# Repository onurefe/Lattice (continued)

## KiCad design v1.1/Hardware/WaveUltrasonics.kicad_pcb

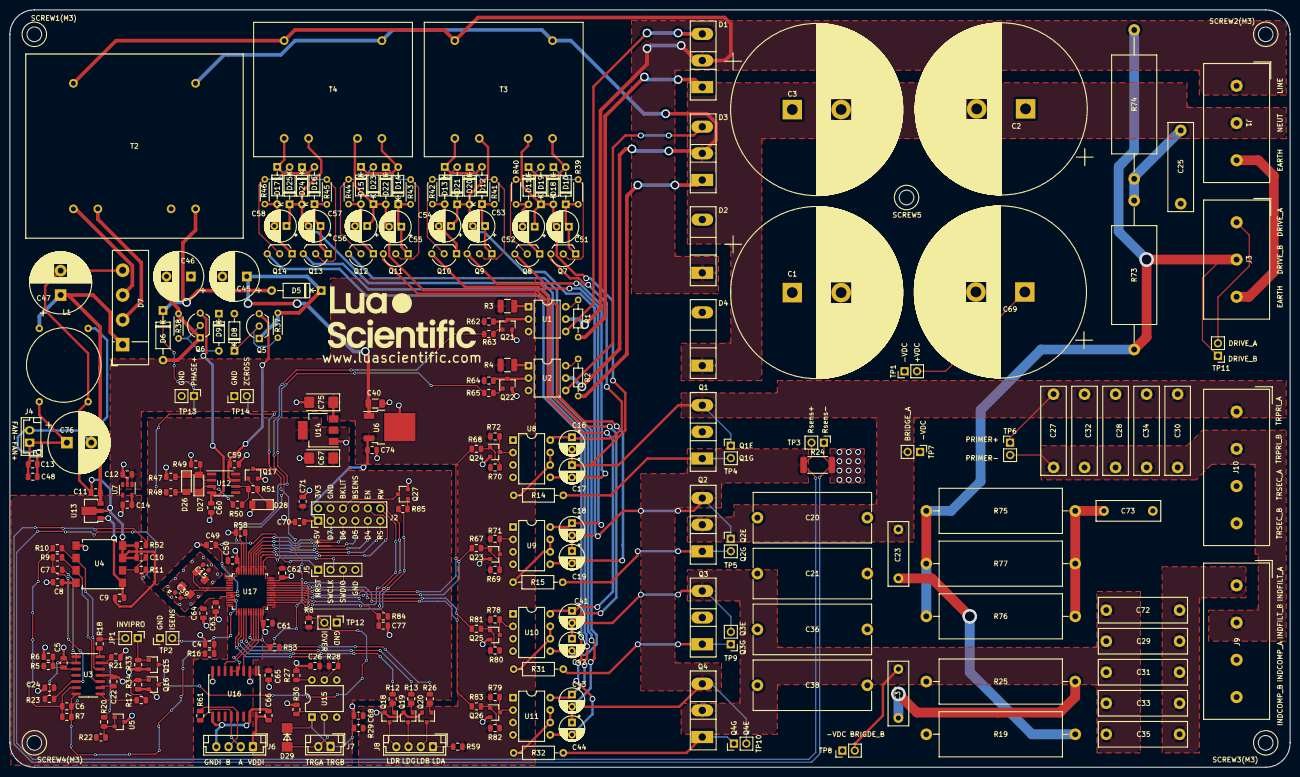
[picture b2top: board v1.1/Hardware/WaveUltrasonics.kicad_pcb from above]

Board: 2 copper layers, 262.0 x 155.0 mm, 257 parts (0 on the bottom side), 155 nets.

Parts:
C1, C2, C3, C69: 470u 400v; CP_Radial_D35.0mm_P10.00mm_SnapIn
C4: 100n; R_0805_2012Metric
C5, C11, C12, C13, C14, C63: 1u; C_0805_2012Metric
C6, C7: 330p; C_0805_2012Metric
C8, C9, C24, C26, C48, C49, C50, C59, C60, C61, C62, C64, C65, C66, C68, C70, C71, C74, C77: 100n; C_0805_2012Metric
C10: 47n; C_0805_2012Metric
C15, C39: 18p; C_0603_1608Metric
C16, C17, C18, C19, C41, C42, C43, C44: 1u 35v; CP_Radial_D5.0mm_P2.50mm
C20, C21, C36, C38: 820n 400VDC; C_Rect_L24.0mm_W10.1mm_P22.50mm_MKT
C22: 2.2u; C_0805_2012Metric
C23, C37, C73: 2.2n 400VAC; C_Rect_L13.0mm_W4.0mm_P10.00mm_FKS3_FKP3_MKS4
C25: 1.5n 400VAC; C_Rect_L18.0mm_W5.0mm_P15.00mm_FKS3_FKP3
C27, C28, C30, C32, C34: 6.8n 400VAC; C_Rect_L18.0mm_W5.0mm_P15.00mm_FKS3_FKP3
C29, C31, C33, C35, C72: 10n; C_Rect_L18.0mm_W5.0mm_P15.00mm_FKS3_FKP3
C40: 1uF 35v; C_1206_3216Metric
C45, C46: 470u 35v; CP_Radial_D10.0mm_P5.00mm
C47, C76: 1000u 35v; CP_Radial_D12.5mm_P5.00mm
C51, C52, C53, C54, C55, C56, C57, C58: 220u; CP_Radial_D6.3mm_P2.50mm
C67, C75: 10uF; CP_EIA-6032-15_Kemet-U
D1, D3: CLA50E1200HB; TO-247-3_Vertical
D2, D4: DSEI60-06A; TO-247-2_Vertical
D5, D6: 1N4007; D_A-405_P10.16mm_Horizontal
D7: D_Bridge_+AA-; Diode_Bridge_Vishay_KBU
D8, D9, D18, D19, D20, D21, D22, D23, D24, D25: 15v; D_DO-35_SOD27_P7.62mm_Horizontal
D10, D11, D12, D13, D14, D15, D16, D17: D; D_DO-35_SOD27_P7.62mm_Horizontal
D26, D27, D28: D; D_MiniMELF
D29: SMAJ6R0CA-HT; DO214AC_SMA
J1: MAINS_IN; DG25C-B-03P-13-00AH
J2: L-KLS1-207-2-12-S; PinHeader_2x06_P2.54mm_Vertical
J3: Screw_Terminal_01x03; DG25C-B-03P-13-00AH
J4, J7: DS1069-02MVW6X; JST_EH_B2B-EH-A_1x02_P2.50mm_Vertical
J5: Conn_01x04; PinHeader_1x04_P2.54mm_Vertical
J6, J8: DS1069-04MVW6X; JST_EH_B4B-EH-A_1x04_P2.50mm_Vertical
J9, J10: DG25C-B-04P-13-00AH
JP1: Jumper_NO_Small; PinHeader_1x02_P2.54mm_Vertical
L1: EMIFilter_LL_2314; EPCOS_B82721A
Q1, Q2, Q3, Q4: IXXH80N65B4H1; TO-247-3_Vertical
Q5, Q7, Q9, Q11, Q13: BC546; TO-92_Inline_Wide
Q6, Q8, Q10, Q12, Q14: BC556; TO-92_Inline_Wide
Q15, Q16, Q17, Q18, Q19, Q20: MMBT3904; SOT-23
Q21, Q22, Q23, Q24, Q25, Q26, Q27: BC817; SOT-23
R1, R2: 1.5k; R_Axial_DIN0204_L3.6mm_D1.6mm_P7.62mm_Horizontal
R3, R4: 51R 1/2Watt; R_1210_3225Metric
R5, R6, R21: 22k %0.1; R_0805_2012Metric
R7, R23: 3.6k %0.1; R_0805_2012Metric
R8, R29, R30, R53, R61, R67, R68, R81, R83, R84: 120R; R_0805_2012Metric
R9, R10: 4.7k %0.1; R_0805_2012Metric
R11: 10R; R_0805_2012Metric
R12, R13, R26, R27, R58: 10k; R_0805_2012Metric
R14, R15, R31, R32: 10R; R_Axial_DIN0207_L6.3mm_D2.5mm_P10.16mm_Horizontal
R16: 33R; R_0805_2012Metric
R17, R18, R22, R28, R63, R65, R85: 2.2k; R_0805_2012Metric
R19, R25: 15R 5W; R_Axial_Power_L25.0mm_W9.0mm_P30.48mm
R20: 20k %0.1; R_0805_2012Metric
R24: 6.8mohm 2W %1; R_2512_6332Metric
R33, R34: 1k; R_0805_2012Metric
R37, R38, R39, R40, R41, R42, R43, R44, R45, R46: 1k; R_Axial_DIN0204_L3.6mm_D1.6mm_P5.08mm_Horizontal
R47, R48, R51, R62, R64: 4.7k; R_0805_2012Metric
R49, R50: 1M; R_0805_2012Metric
R52: 0R; R_0805_2012Metric
R59: 220R; R_0805_2012Metric
R69, R70, R80, R82: 8.2k; R_0805_2012Metric
R71, R72, R78, R79: 82R; R_0805_2012Metric
R73, R74: 22k 7W; R_Axial_DIN0922_L20.0mm_D9.0mm_P30.48mm_Horizontal
R75, R76, R77: 4.7k 5W; R_Axial_Power_L25.0mm_W9.0mm_P30.48mm
T2: Transformer_1P_2S; ASL151212
T3, T4: Transformer_1P_2S; ASL102212
TP1, TP2, TP3, TP4, TP5, TP6, TP7, TP8, TP9, TP10, TP11, TP12, TP13, TP14: TestPoint_2Pole; PinHeader_1x02_P2.54mm_Vertical
U1, U2: 4N39; DIP-6_W7.62mm
U3: MCP6024; SOIC-14_3.9x8.7mm_P1.27mm
U4: ACPL-7900; SSO-8_6.7x9.8mm_P2.54mm_Clearance8mm
U5: TL431LP; SOT-23
U6: L7805; TO-252-2
U7: TLV73333PDBV; SOT-23-5
U8, U9, U10, U11: HCPL-3120; DIP-8_W7.62mm
U12: OPA228; SOIC-8_3.9x4.9mm_P1.27mm
U13: L78L05_SOT89; SOT-89-3
U14: TLV1117-33; SOT-223-3_TabPin2
U15: 4N25; DIP-6_W7.62mm
U16: ADM2483xRW; SOIC-16W_7.5x10.3mm_P1.27mm
U17: STM32F334C8Tx; LQFP-48_7x7mm_P0.5mm
Y1: 8MHz; Crystal_5x3.2mm_4leads

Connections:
+5V: C12.2, C68.2, C70.1, C74.2, C75.1, J2.1, R3.2, R4.2, R29.2, R59.2, R62.2, R64.2, R69.2, R70.2, R71.1, R72.1, R78.1, R79.1, R80.2, R82.2, U6.3 (OUT), U7.1 (IN), U7.3 (EN), U14.3 (VI)
+15V: C59.1, Q5.3 (E), U12.7 (V+)
+VDC: C1.1, C2.1, C3.1, C20.2, C21.2, C36.2, C38.2, C69.1, D1.1 (K), D3.1 (K), Q1.2 (C), Q3.2 (C), R1.2, R2.2, TP1.2
-15V: C60.1, Q6.3 (E), U12.4 (V-)
-VDC: C1.2, C2.2, C3.2, C20.1, C21.1, C36.1, C38.1, C69.2, D2.2 (A), D4.2 (A), R19.2, R24.2, R25.2, R52.2, TP1.1, TP3.1, TP7.1, TP8.1
/GATE1_GND: C16.2, C17.1, C23.1, C27.2, C28.2, C30.2, C32.2, C34.2, C51.2, C52.1, D18.2 (A), D19.1 (K), J10.1, Q1.3 (E), Q2.2 (C), T3.4 (SB), TP4.1, TP6.1, TP7.2
/GATE1_V+: C16.1, Q7.3 (E), U8.8 (VCC)
/GATE1_V-: C17.2, Q8.3 (E), U8.5 (VEE)
/GATE2_V+: C18.1, Q9.3 (E), U9.8 (VCC)
/GATE2_V-: C19.2, Q10.3 (E), U9.5 (VEE)
/GATE3_GND: C29.1, C31.1, C33.1, C35.1, C37.1, C41.2, C42.1, C55.2, C56.1, C72.1, D22.2 (A), D23.1 (K), Q3.3 (E), Q4.2 (C), T4.4 (SB), TP8.2, TP9.2
/GATE3_V+: C41.1, Q11.3 (E), U10.8 (VCC)
/GATE3_V-: C42.2, Q12.3 (E), U10.5 (VEE)
/GATE4_V+: C43.1, Q13.3 (E), U11.8 (VCC)
/GATE4_V-: C44.2, Q14.3 (E), U11.5 (VEE)
/ISENS: C4.1, R16.1, TP2.2, U17.10 (PA0)
/LED_BLUE: R26.1, U17.17 (PA7)
/LED_GREEN: R13.1, U17.16 (PA6)
/LED_RED: R12.1, U17.15 (PA5)
/Mcu/LCD_BKLIGHT: R85.2, U17.26 (PB13)
/Mcu/LCD_BSENS: J2.8, R84.1
/Mcu/LCD_D4: J2.9, U17.40 (PB4)
/Mcu/LCD_D5: J2.7, U17.41 (PB5)
/Mcu/LCD_D6: J2.5, U17.42 (PB6)
/Mcu/LCD_D7: J2.3, U17.43 (PB7)
/Mcu/LCD_EN: J2.10, U17.38 (PA15)
/Mcu/LCD_RS: J2.11, U17.39 (PB3)
/Mcu/LCD_R~W: J2.12, U17.28 (PB15)
/Mcu/NRST: C49.1, J5.1, U17.7 (NRST)
/Mcu/SWCLK: J5.2, U17.37 (PA14)
/Mcu/SWDIO: J5.3, U17.34 (PA13)
/OVERCURRENT: Q15.3 (C), Q16.3 (C), R8.1, TP12.2, U17.33 (PA12)
/PHASE+: D5.2 (A), D6.1 (K), R48.1, T2.3 (SA), TP13.1
/RS485_DE~RE: U16.4 (~RE), U16.5 (DE), U17.20 (PB2)
/RS485_RX: U16.3 (RxD), U17.22 (PB11)
/RS485_TX: U16.6 (TxD), U17.21 (PB10)
/RSENS+: C18.2, C19.1, C43.2, C44.1, C53.2, C54.1, C57.2, C58.1, D20.2 (A), D21.1 (K), D24.2 (A), D25.1 (K), Q2.3 (E), Q4.3 (E), R11.2, R24.1, T3.5 (SC), T4.5 (SC), TP3.2, TP5.1, TP10.2
/THRISTOR0_DRV: R63.2, U17.45 (PB8)
/THRISTOR1_DRV: R65.2, U17.46 (PB9)
/TRIGOUT: R28.1, U15.5, U17.13 (PA3), U17.14 (PA4)
/ZERO_CROSSING: Q17.3 (C), R53.1, TP14.2, U17.18 (PB0), U17.19 (PB1)
/~HBRIDGE_A_HSIDE: R68.2, U17.29 (PA8)
/~HBRIDGE_A_LSIDE: R67.2, U17.30 (PA9)
/~HBRIDGE_B_HSIDE: R81.1, U17.31 (PA10)
/~HBRIDGE_B_LSIDE: R83.1, U17.32 (PA11)
Earth_Protective: J1.3, J3.3
GND: C4.2, C5.1, C8.1, C12.1, C14.1, C15.1, C22.2, C24.2, C26.2, C39.1, C40.2, C45.2, C46.1, C49.2, C50.2, C59.2, C60.2, C61.2, C62.2, C63.2, C64.1, C65.1, C67.2, C68.1, C70.2, C71.1, C74.1, C75.2, C77.1, D8.2 (A), D9.1 (K), D28.2 (A), J2.4, J5.4, Q15.2 (E), Q16.2 (E), Q17.2 (E), Q18.2 (E), Q19.2 (E), Q20.2 (E), Q21.2 (E), Q22.2 (E), Q23.2 (E), Q24.2 (E), Q25.2 (E), Q26.2 (E), Q27.2 (E), R6.1, R21.1, R27.1, R30.1, R33.1, R34.1, R47.1, R49.2, R58.2, T2.4 (SB), TP2.1, TP12.1, TP13.2, TP14.1, U3.11 (V-), U4.5 (GND2), U5.3 (A), U6.2 (GND), U7.2 (GND), U8.3 (C), U9.3 (C), U10.3 (C), U11.3 (C), U14.1 (GND), U15.4, U16.2 (GND1), U16.8 (GND1), U17.8 (VSSA), U17.23 (VSS), U17.35 (VSS), U17.47 (VSS), Y1.2, Y1.4
GND1: C9.1, C10.2, C11.1, C47.2, D7.4 (-), L1.4, R52.1, U4.3 (IN-), U4.4 (GND1), U13.2 (GND)
GND2: C13.1, C48.1, C76.2, J4.2, L1.3
LINE: D1.2 (A), D2.1 (K), J1.1, T2.1 (AA), T3.1 (AA), T4.1 (AA), U1.5 (DAN)
NEUT: D3.2 (A), D4.1 (K), J1.2, T2.2 (AB), T3.2 (AB), T4.2 (AB), U2.5 (DAN)
unnamed: C5.2, R5.1, R6.2, U3.3 (+)
unnamed: C6.1, R7.2, R10.2, U3.6 (-)
unnamed: C6.2, R7.1, R16.2, U3.7
unnamed: C7.1, R23.1, U3.1, U3.2 (-)
unnamed: C7.2, R9.2, R23.2, U3.5 (+)
unnamed: C9.2, U4.1 (VDD1), U13.1 (OUT)
unnamed: C10.1, R11.1, U4.2 (IN+)
unnamed: C15.2, U17.5 (PF0), Y1.3
unnamed: C22.1, R20.2, R21.2, U3.9 (-), U3.13 (-)
unnamed: C23.2, R19.1
unnamed: C25.1, C73.1, J3.1, J9.4, J10.4, TP11.2
unnamed: C25.2, R73.1, R74.1
unnamed: C27.1, C28.1, C30.1, C32.1, C34.1, J9.2, J10.2, TP6.2
unnamed: C29.2, C31.2, C33.2, C35.2, C72.2, J9.1
unnamed: C37.2, R25.1
unnamed: C39.2, U17.6 (PF1), Y1.1
unnamed: C46.2, D6.2 (A), Q6.1 (C), R38.2
unnamed: C51.1, D10.1 (K), Q7.1 (C), R39.1
unnamed: C52.2, D11.2 (A), Q8.1 (C), R40.2
unnamed: C53.1, D12.1 (K), Q9.1 (C), R41.1
unnamed: C54.2, D13.2 (A), Q10.1 (C), R42.2
unnamed: C55.1, D14.1 (K), Q11.1 (C), R43.1
unnamed: C56.2, D15.2 (A), Q12.1 (C), R44.2
unnamed: C57.1, D16.1 (K), Q13.1 (C), R45.1
unnamed: C58.2, D17.2 (A), Q14.1 (C), R46.2
unnamed: C66.1, J6.4, U16.9 (GND2), U16.15 (GND2)
unnamed: C66.2, J6.1, U16.16 (VDD2)
unnamed: C73.2, R75.1, R76.1, R77.1
unnamed: C77.2, R84.2, U17.27 (PB14)
unnamed: D1.3 (G), U1.4 (DCAT)
unnamed: D3.3 (G), U2.4 (DCAT)
unnamed: D7.2 (~~), T2.5 (SC)
unnamed: D7.3 (~~), T2.6 (SD)
unnamed: D8.1 (K), Q5.2 (B), R37.2
unnamed: D9.2 (A), Q6.2 (B), R38.1
unnamed: D10.2 (A), D11.1 (K), T3.3 (SA)
unnamed: D12.2 (A), D13.1 (K), T3.6 (SD)
unnamed: D14.2 (A), D15.1 (K), T4.3 (SA)
unnamed: D16.2 (A), D17.1 (K), T4.6 (SD)
unnamed: D18.1 (K), Q7.2 (B), R39.2
unnamed: D19.2 (A), Q8.2 (B), R40.1
unnamed: D20.1 (K), Q9.2 (B), R41.2
unnamed: D21.2 (A), Q10.2 (B), R42.1
unnamed: D22.1 (K), Q11.2 (B), R43.2
unnamed: D23.2 (A), Q12.2 (B), R44.1
unnamed: D24.1 (K), Q13.2 (B), R45.2
unnamed: D25.2 (A), Q14.2 (B), R46.1
unnamed: D26.1 (K), D27.2 (A), R47.2, R49.1, U12.2 (-)
unnamed: D26.2 (A), D27.1 (K), R48.2, R50.1, U12.3 (+)
unnamed: D28.1 (K), Q17.1 (B), R51.1
unnamed: D29.1 (A1), J7.1, R29.1, U15.1
unnamed: D29.2 (A2), J7.2, R30.2, U15.2
unnamed: J2.6, Q27.3 (C)
unnamed: J6.2, R61.2, U16.12 (A)
unnamed: J6.3, R61.1, U16.13 (B)
unnamed: J8.1, R59.1
unnamed: J8.2, Q20.3 (C)
unnamed: J8.3, Q19.3 (C)
unnamed: J8.4, Q18.3 (C)
unnamed: J3.2, J9.3, J10.3, R73.2, R74.2, R75.2, R76.2, R77.2, TP11.1
unnamed: JP1.1, Q15.1 (B), R33.2
unnamed: JP1.2, R18.1
unnamed: Q1.1 (G), R14.2, TP4.2
unnamed: Q2.1 (G), R15.2, TP5.2
unnamed: Q3.1 (G), R31.1, TP9.1
unnamed: Q4.1 (G), R32.1, TP10.1
unnamed: Q16.1 (B), R17.1, R34.2
unnamed: Q18.1 (B), R12.2
unnamed: Q19.1 (B), R13.2
unnamed: Q20.1 (B), R26.2
unnamed: Q21.1 (B), R63.1
unnamed: Q21.3 (C), R62.1, U1.2 (ECAT)
unnamed: Q22.1 (B), R65.1
unnamed: Q22.3 (C), R64.1, U2.2 (ECAT)
unnamed: Q23.1 (B), R67.1, R69.1
unnamed: Q23.3 (C), R71.2, U9.2 (A)
unnamed: Q24.1 (B), R68.1, R70.1
unnamed: Q24.3 (C), R72.2, U8.2 (A)
unnamed: Q25.1 (B), R80.1, R81.2
unnamed: Q25.3 (C), R78.2, U10.2 (A)
unnamed: Q26.1 (B), R82.1, R83.2
unnamed: Q26.3 (C), R79.2, U11.2 (A)
unnamed: Q27.1 (B), R85.1
unnamed: R1.1, U1.6 (DGAT)
unnamed: R2.1, U2.6 (DGAT)
unnamed: R3.1, U1.1 (EAN)
unnamed: R4.1, U2.1 (EAN)
unnamed: R9.1, U3.10 (+), U4.7 (OUT+)
unnamed: R10.1, U3.12 (+), U4.6 (OUT-)
unnamed: R14.1, U8.6 (VO), U8.7 (VO)
unnamed: R15.1, U9.6 (VO), U9.7 (VO)
unnamed: R17.2, U3.8
unnamed: R18.2, U3.14
unnamed: R20.1, R22.1, U5.1 (K), U5.2 (REF)
unnamed: R27.2, U15.6
unnamed: R31.2, U10.6 (VO), U10.7 (VO)
unnamed: R32.2, U11.6 (VO), U11.7 (VO)
unnamed: R50.2, R51.2, U12.6
unnamed: R58.1, U17.44 (BOOT0)
VCC: C40.1, C45.1, D5.1 (K), Q5.1 (C), R37.1, U6.1 (IN)
VDD: C26.1, C50.1, C61.1, C62.1, C65.2, C67.1, C71.2, J2.2, R8.2, R28.2, R53.2, U14.2 (VO), U16.1 (VDD1), U17.1 (VBAT), U17.24 (VDD), U17.36 (VDD), U17.48 (VDD)
VDDA: C8.2, C14.2, C24.1, C63.1, C64.2, R5.2, R22.2, U3.4 (V+), U4.8 (VDD2), U7.5 (OUT), U17.9 (VDDA)
VEE: C11.2, C47.1, D7.1 (+), L1.2, U13.3 (IN)
Vdrive: C13.2, C48.2, C76.1, J4.1, L1.1

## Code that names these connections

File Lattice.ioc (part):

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Mcu.Name=STM32F334C(4-6-8)Tx
Mcu.Package=LQFP48
Mcu.UserName=STM32F334C8Tx
PA0.GPIOParameters=GPIO_Label
PA0.GPIO_Label=ISENS+
PA0.Mode=IN1-Differential
PA0.Signal=ADC1_IN1
PA1.GPIOParameters=GPIO_Label
PA1.GPIO_Label=ISENS-
PA1.Mode=IN1-Differential
PA1.Signal=ADC1_IN2
PA10.Mode=Output_TB1TB2
PA10.Signal=HRTIM1_CHB1
PA11.Mode=Output_TB1TB2
PA11.Signal=HRTIM1_CHB2
PA12.GPIOParameters=GPIO_Label
PA12.GPIO_Label=OVERCURRENT
PA12.Mode=Fault_Enable1
PA12.Signal=HRTIM1_FLT1
PA13.Mode=Serial_Wire
PA13.Signal=SYS_JTMS-SWDIO
PA14.Mode=Serial_Wire
PA14.Signal=SYS_JTCK-SWCLK
PA15.GPIOParameters=GPIO_Label
PA15.GPIO_Label=LCD_RS
PA15.Signal=GPIO_Output
PA2.GPIOParameters=GPIO_Label
PA2.GPIO_Label=VSENS+
PA2.Mode=IN3-Differential
PA2.Signal=ADC1_IN3
PA3.GPIOParameters=GPIO_Label
PA3.GPIO_Label=VSENS-
PA3.Mode=IN3-Differential
PA3.Signal=ADC1_IN4
PA4.GPIOParameters=GPIO_Label
PA4.GPIO_Label=TRGIN_RISING
PA4.Signal=GPXTI4
PA5.GPIOParameters=GPIO_Label
PA5.GPIO_Label=TRGIN_FALLING
PA5.Signal=GPXTI5
PA6.GPIOParameters=GPIO_Label
PA6.GPIO_Label=LED_RED
PA6.Signal=GPIO_Output
PA7.GPIOParameters=GPIO_Label
PA7.GPIO_Label=LED_GREEN
PA7.Signal=GPIO_Output
PA8.Mode=Output_TA1TA2
PA8.Signal=HRTIM1_CHA1
PA9.Mode=Output_TA1TA2
PA9.Signal=HRTIM1_CHA2
PB0.GPIOParameters=GPIO_Label
PB0.GPIO_Label=ZC_RISING_DETECT
PB0.Signal=S_TIM3_CH3
PB1.GPIOParameters=GPIO_Label
PB1.GPIO_Label=ZC_FALLING_DETECT
PB1.Signal=S_TIM3_CH4
PB10.GPIOParameters=GPIO_Label
PB10.GPIO_Label=RS485_TX
PB10.Mode=Asynchronous
PB10.Signal=USART3_TX
PB11.GPIOParameters=GPIO_Label
PB11.GPIO_Label=RS485_RX
PB11.Mode=Asynchronous
PB11.Signal=USART3_RX
PB12.GPIOParameters=GPIO_Label
PB12.GPIO_Label=LED_BLUE
PB12.Signal=GPIO_Output
PB14.GPIOParameters=GPIO_Label
PB14.GPIO_Label=LCD_BSENS
PB14.Mode=IN14-Single-Ended
PB14.Signal=ADC2_IN14
PB15.GPIOParameters=GPIO_Label
PB15.GPIO_Label=LCD_RnW
PB15.Signal=GPIO_Output
PB2.GPIOParameters=GPIO_Label
PB2.GPIO_Label=RS485_DEnRE
PB2.Signal=GPIO_Output
PB3.GPIOParameters=GPIO_Label
PB3.GPIO_Label=LCD_EN
PB3.Signal=GPIO_Output
PB4.GPIOParameters=GPIO_Label
PB4.GPIO_Label=LCD_D4
PB4.Signal=GPIO_Output
PB5.GPIOParameters=GPIO_Label
PB5.GPIO_Label=LCD_D5
PB5.Signal=GPIO_Output
PB6.GPIOParameters=GPIO_Label
PB6.GPIO_Label=LCD_D6
PB6.Signal=GPIO_Output
PB7.GPIOParameters=GPIO_Label
PB7.GPIO_Label=LCD_D7
PB7.Signal=GPIO_Output
PB8.GPIOParameters=GPIO_Label
PB8.GPIO_Label=THYRISTOR0_DRIVE
PB8.Signal=GPIO_Output
PB9.GPIOParameters=GPIO_Label
PB9.GPIO_Label=THYRISTOR1_DRIVE
PB9.Signal=GPIO_Output
PC13.GPIOParameters=GPIO_Label
PC13.GPIO_Label=LED_RED
PC13.Signal=GPIO_Output
PC14\ /\ OSC32_IN.GPIOParameters=GPIO_Label
PC14\ /\ OSC32_IN.GPIO_Label=LED_BLUE
PC14\ /\ OSC32_IN.Signal=GPIO_Output
PF0\ /\ OSC_IN.Mode=HSE-External-Oscillator
PF0\ /\ OSC_IN.Signal=RCC_OSC_IN
PF1\ /\ OSC_OUT.Mode=HSE-External-Oscillator
PF1\ /\ OSC_OUT.Signal=RCC_OSC_OUT
RCC.HSEPLLFreq_Value=8000000
RCC.HSE_VALUE=8000000
RCC.SYSCLKFreq_VALUE=8000000
board=custom

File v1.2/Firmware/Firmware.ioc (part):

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Mcu.Name=STM32F334C(4-6-8)Tx
Mcu.Package=LQFP48
Mcu.UserName=STM32F334C8Tx
PA0.GPIOParameters=GPIO_Label
PA0.GPIO_Label=ISENS+
PA0.Mode=IN1-Differential
PA0.Signal=ADC1_IN1
PA1.GPIOParameters=GPIO_Label
PA1.GPIO_Label=ISENS-
PA1.Mode=IN1-Differential
PA1.Signal=ADC1_IN2
PA13.Mode=Serial_Wire
PA13.Signal=SYS_JTMS-SWDIO
PA14.Mode=Serial_Wire
PA14.Signal=SYS_JTCK-SWCLK
PA2.GPIOParameters=GPIO_Label
PA2.GPIO_Label=VSENS+
PA2.Mode=IN3-Differential
PA2.Signal=ADC1_IN3
PA3.GPIOParameters=GPIO_Label
PA3.GPIO_Label=VSENS-
PA3.Mode=IN3-Differential
PA3.Signal=ADC1_IN4
PA4.GPIOParameters=GPIO_PuPd,GPIO_Label
PA4.GPIO_Label=TRIGIN_RISING
PA4.GPIO_PuPd=GPIO_PULLDOWN
PA4.Signal=GPXTI4
PA5.GPIOParameters=GPIO_PuPd,GPIO_Label
PA5.GPIO_Label=TRIGIN_FALLING
PA5.GPIO_PuPd=GPIO_PULLDOWN
PA5.Signal=GPXTI5
PA8.GPIOParameters=GPIO_Label
PA8.GPIO_Label=HB_HSIDE
PA8.Mode=Output_TA1TA2
PA8.Signal=HRTIM1_CHA1
PA9.GPIOParameters=GPIO_Label
PA9.GPIO_Label=HB_LSIDE
PA9.Mode=Output_TA1TA2
PA9.Signal=HRTIM1_CHA2
PB0.GPIOParameters=GPIO_Label
PB0.GPIO_Label=ZC_RISING_DETECT
PB0.Signal=S_TIM3_CH3
PB1.GPIOParameters=GPIO_Label
PB1.GPIO_Label=ZC_FALLING_DETECT
PB1.Signal=S_TIM3_CH4
PB10.GPIOParameters=GPIO_Label
PB10.GPIO_Label=RS485_TX
PB10.Mode=Asynchronous
PB10.Signal=USART3_TX
PB11.GPIOParameters=GPIO_Label
PB11.GPIO_Label=RS485_RX
PB11.Mode=Asynchronous
PB11.Signal=USART3_RX
PB12.GPIOParameters=GPIO_Label
PB12.GPIO_Label=LED_RED
PB12.Signal=GPIO_Output
PB13.GPIOParameters=GPIO_Label
PB13.GPIO_Label=LED_GREEN
PB13.Signal=GPIO_Output
PB14.GPIOParameters=GPIO_Label
PB14.GPIO_Label=LED_BLUE
PB14.Signal=GPIO_Output
PB2.GPIOParameters=GPIO_Speed,PinState,GPIO_Label
PB2.GPIO_Label=RS485_DEnRE
PB2.GPIO_Speed=GPIO_SPEED_FREQ_MEDIUM
PB2.PinState=GPIO_PIN_RESET
PB2.Signal=GPIO_Output
PB3.GPIOParameters=GPIO_Label
PB3.GPIO_Label=MISC0
PB3.Signal=GPIO_Output
PB4.GPIOParameters=GPIO_Label
PB4.GPIO_Label=MISC1
PB4.Signal=GPIO_Output
PB5.GPIOParameters=GPIO_Label
PB5.GPIO_Label=MISC2
PB5.Signal=GPIO_Output
PB6.GPIOParameters=GPIO_Label
PB6.GPIO_Label=HMI_SELF_TX
PB6.Mode=Asynchronous
PB6.Signal=USART1_TX
PB7.GPIOParameters=GPIO_Label
PB7.GPIO_Label=HMI_SELF_RX
PB7.Mode=Asynchronous
PB7.Signal=USART1_RX
PB8.GPIOParameters=GPIO_Speed,GPIO_Label
PB8.GPIO_Label=THYRISTOR0_DRIVE
PB8.GPIO_Speed=GPIO_SPEED_FREQ_MEDIUM
PB8.Signal=GPIO_Output
PB9.GPIOParameters=GPIO_Speed,GPIO_Label
PB9.GPIO_Label=THYRISTOR1_DRIVE
PB9.GPIO_Speed=GPIO_SPEED_FREQ_MEDIUM
PB9.Signal=GPIO_Output
PF0\ /\ OSC_IN.Mode=HSE-External-Oscillator
PF0\ /\ OSC_IN.Signal=RCC_OSC_IN
PF1\ /\ OSC_OUT.Mode=HSE-External-Oscillator
PF1\ /\ OSC_OUT.Signal=RCC_OSC_OUT
RCC.HSEPLLFreq_Value=8000000
RCC.HSE_VALUE=8000000
RCC.SYSCLKFreq_VALUE=72000000
RCC.SYSCLKSourceVirtual=RCC_SYSCLKSOURCE_PLLCLK
board=custom

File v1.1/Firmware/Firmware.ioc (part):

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Mcu.Name=STM32F103C(8-B)Tx
Mcu.Package=LQFP48
Mcu.UserName=STM32F103CBTx
PA0-WKUP.GPIOParameters=GPIO_Label
PA0-WKUP.GPIO_Label=CURRENT_SENS
PA0-WKUP.Signal=ADCx_IN0
PA13.Mode=Serial_Wire
PA13.Signal=SYS_JTMS-SWDIO
PA14.Mode=Serial_Wire
PA14.Signal=SYS_JTCK-SWCLK
PA4.GPIOParameters=GPIO_Label
PA4.GPIO_Label=LED_BLUE
PA4.Signal=GPIO_Output
PA5.GPIOParameters=GPIO_Label
PA5.GPIO_Label=LED_RED
PA5.Signal=GPIO_Output
PA6.GPIOParameters=GPIO_Label
PA6.GPIO_Label=THYRISTOR0_DRIVE
PA6.Signal=GPIO_Output
PA7.GPIOParameters=GPIO_Label
PA7.GPIO_Label=THYRISTOR1_DRIVE
PA7.Signal=GPIO_Output
PA8.GPIOParameters=GPIO_Label
PA8.GPIO_Label=HBRIDGE_A_HSIDE
PA8.Signal=S_TIM1_CH1
PA9.GPIOParameters=GPIO_Label
PA9.GPIO_Label=HBRIDGE_B_LSIDE
PA9.Signal=S_TIM1_CH2
PB0.GPIOParameters=GPIO_Label
PB0.GPIO_Label=ZERO_CROSSING_RISING_DETECT
PB0.Signal=S_TIM3_CH3
PB1.GPIOParameters=GPIO_Label
PB1.GPIO_Label=ZERO_CROSSING_FALLING_DETECT
PB1.Signal=S_TIM3_CH4
PB10.GPIOParameters=GPIO_Label
PB10.GPIO_Label=SELF_OUT
PB10.Mode=Asynchronous
PB10.Signal=USART3_TX
PB11.GPIOParameters=GPIO_Label
PB11.GPIO_Label=SELF_IN
PB11.Mode=Asynchronous
PB11.Signal=USART3_RX
PB12.GPIOParameters=GPIO_Label
PB12.GPIO_Label=OVERCURRENT_SENS
PB12.Mode=Activate-Break-Input
PB12.Signal=TIM1_BKIN
PB13.GPIOParameters=GPIO_Label
PB13.GPIO_Label=HBRIDGE_A_LSIDE
PB13.Mode=PWM Generation1 CH1 CH1N
PB13.Signal=TIM1_CH1N
PB14.GPIOParameters=GPIO_Label
PB14.GPIO_Label=HBRIDGE_B_HSIDE
PB14.Mode=PWM Generation2 CH2 CH2N
PB14.Signal=TIM1_CH2N
PD0-OSC_IN.Mode=HSE-External-Oscillator
PD0-OSC_IN.Signal=RCC_OSC_IN
PD1-OSC_OUT.Mode=HSE-External-Oscillator
PD1-OSC_OUT.Signal=RCC_OSC_OUT
RCC.SYSCLKFreq_VALUE=72000000
RCC.SYSCLKSource=RCC_SYSCLKSOURCE_PLLCLK
board=custom

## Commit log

2020-06-07 Only tested on the beta version of v1.0(nearly compatible for the firm).
2020-06-24 v1.1&v1.2 PCB addition.
    #####v1.1#####
    +Change of MCU; STM32F334C8T6 instead of STM32F103C8T6.
    +Filtering 3rd order components of the square wave.
    +Use 4 capacitors.
    +Adapted to generic transformer(primary 6.4mH, secondary 14.4mH)
    +Faster IGBT.
2020-07-08 Addition of firmware to v1.2(not tested)
    +Addition of power tracking(with duty cycle control).
    +Addition of resonance freq tracking(via proprietary algorithm relied on active and reactive power measurements)
    +Quality factor monitoring
    +Power boost when loaded(idle and loaded modes)
    +Much better frequency resolution(less than 1Hz)
2020-09-02 Start of rs485 communication interface development.
2020-09-02 Simulations added.
2020-09-09 Redesign.
    +Cli interface.
    +Modularity improvement(complex number and pid modules created)
    +Range change.
    +Core-Lattice seperated.
    +Improvement of the control function
2020-09-10 Progress in redesign. Error detection addition.
2020-09-10 Lattice state machine polishing, improvements of error monitoring.
2020-09-11 Well defined function set and commented code. Untested.
2020-09-11 Voltage and current processing bugfix and addition of related unit test.
    +Imaginary component had sign error.
    +getPhasors function wasn't returning value.
2020-09-11 Test of PID and Polynomial regression modules.
2020-09-13 Builded firmware. Python script development to factory configuration.
2020-09-14 Python parser module added and tested.
2020-10-27 Serial interface development. Manual added. Untested.
2020-10-27 v1.3 Schematic, footprints and BOM updated.
2020-10-29 v1.3 Layout added & schematic update.
